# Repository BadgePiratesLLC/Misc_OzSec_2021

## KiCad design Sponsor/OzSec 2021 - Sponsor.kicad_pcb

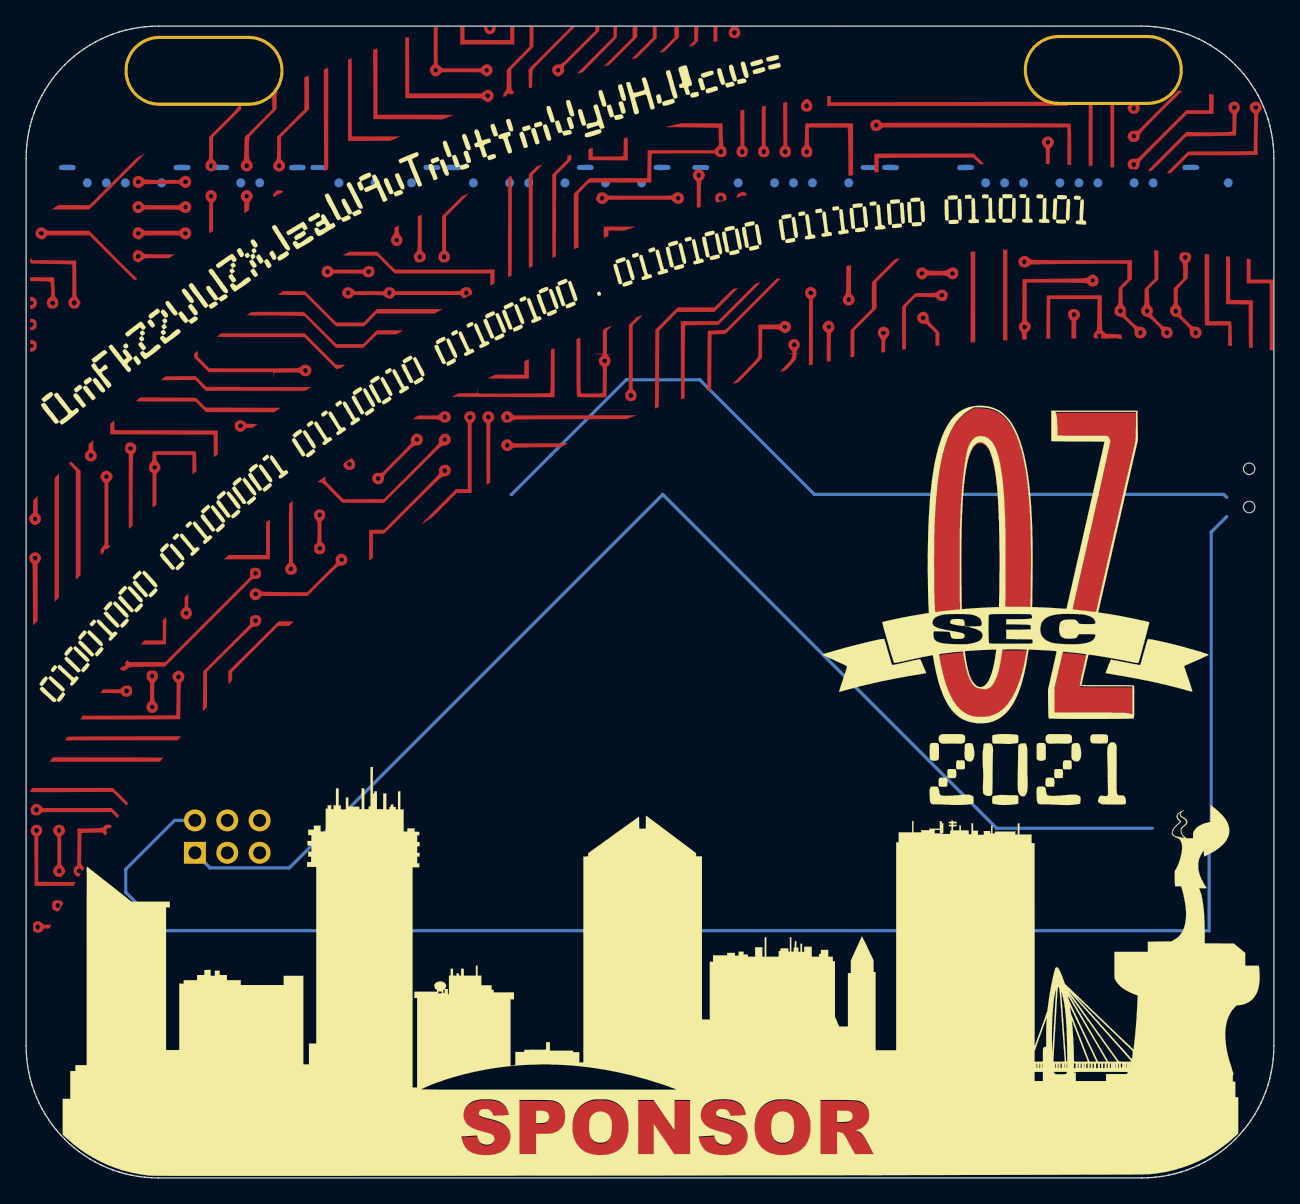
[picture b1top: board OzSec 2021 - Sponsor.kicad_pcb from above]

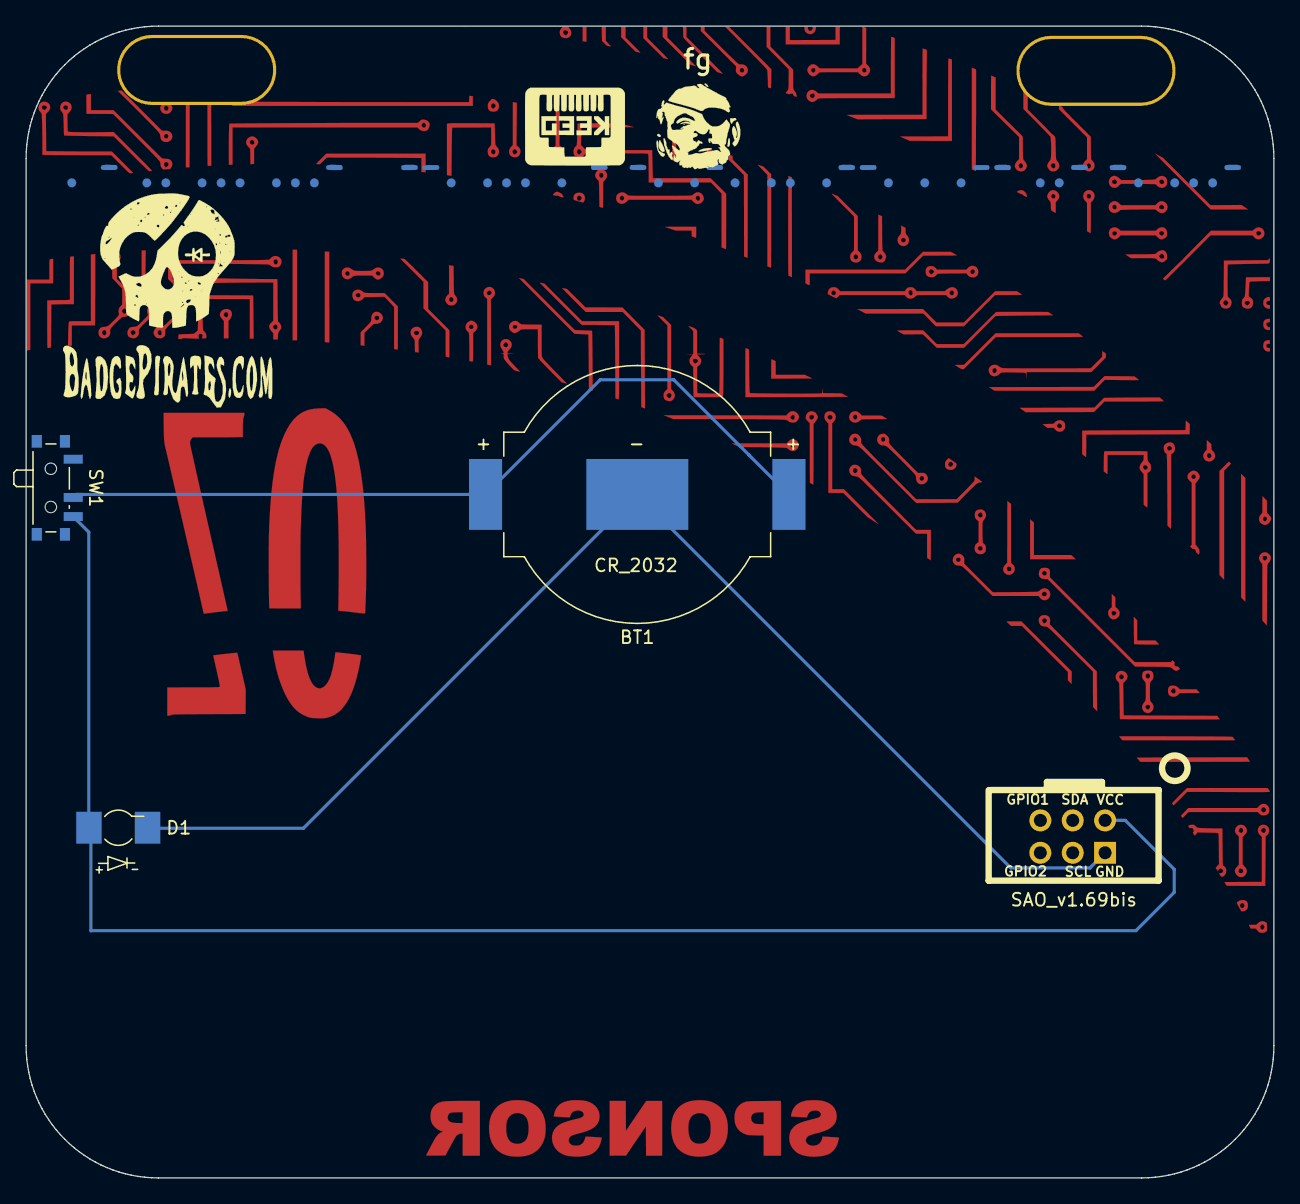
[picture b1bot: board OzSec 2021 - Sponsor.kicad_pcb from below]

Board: 2 copper layers, 97.9 x 90.4 mm, 4 parts (3 on the bottom side), 3 nets.

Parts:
BT1: Battery_Cell; BatteryHolder_MPD_BC2003_1x2032
D1: LED; LED_Osram_Lx_P47F_D2mm_ReverseMount_MaskNoHole
SW1: SW_DPDT_x2; SW_SPDT_PCM12
X1: SAO_v1.69bis; Badgelife-SAOv169-BADGE-2x3_Back

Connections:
GND: BT1.2, D1.1, X1.2
unnamed: BT1.1, SW1.2
VCC: D1.2, SW1.3, X1.1
